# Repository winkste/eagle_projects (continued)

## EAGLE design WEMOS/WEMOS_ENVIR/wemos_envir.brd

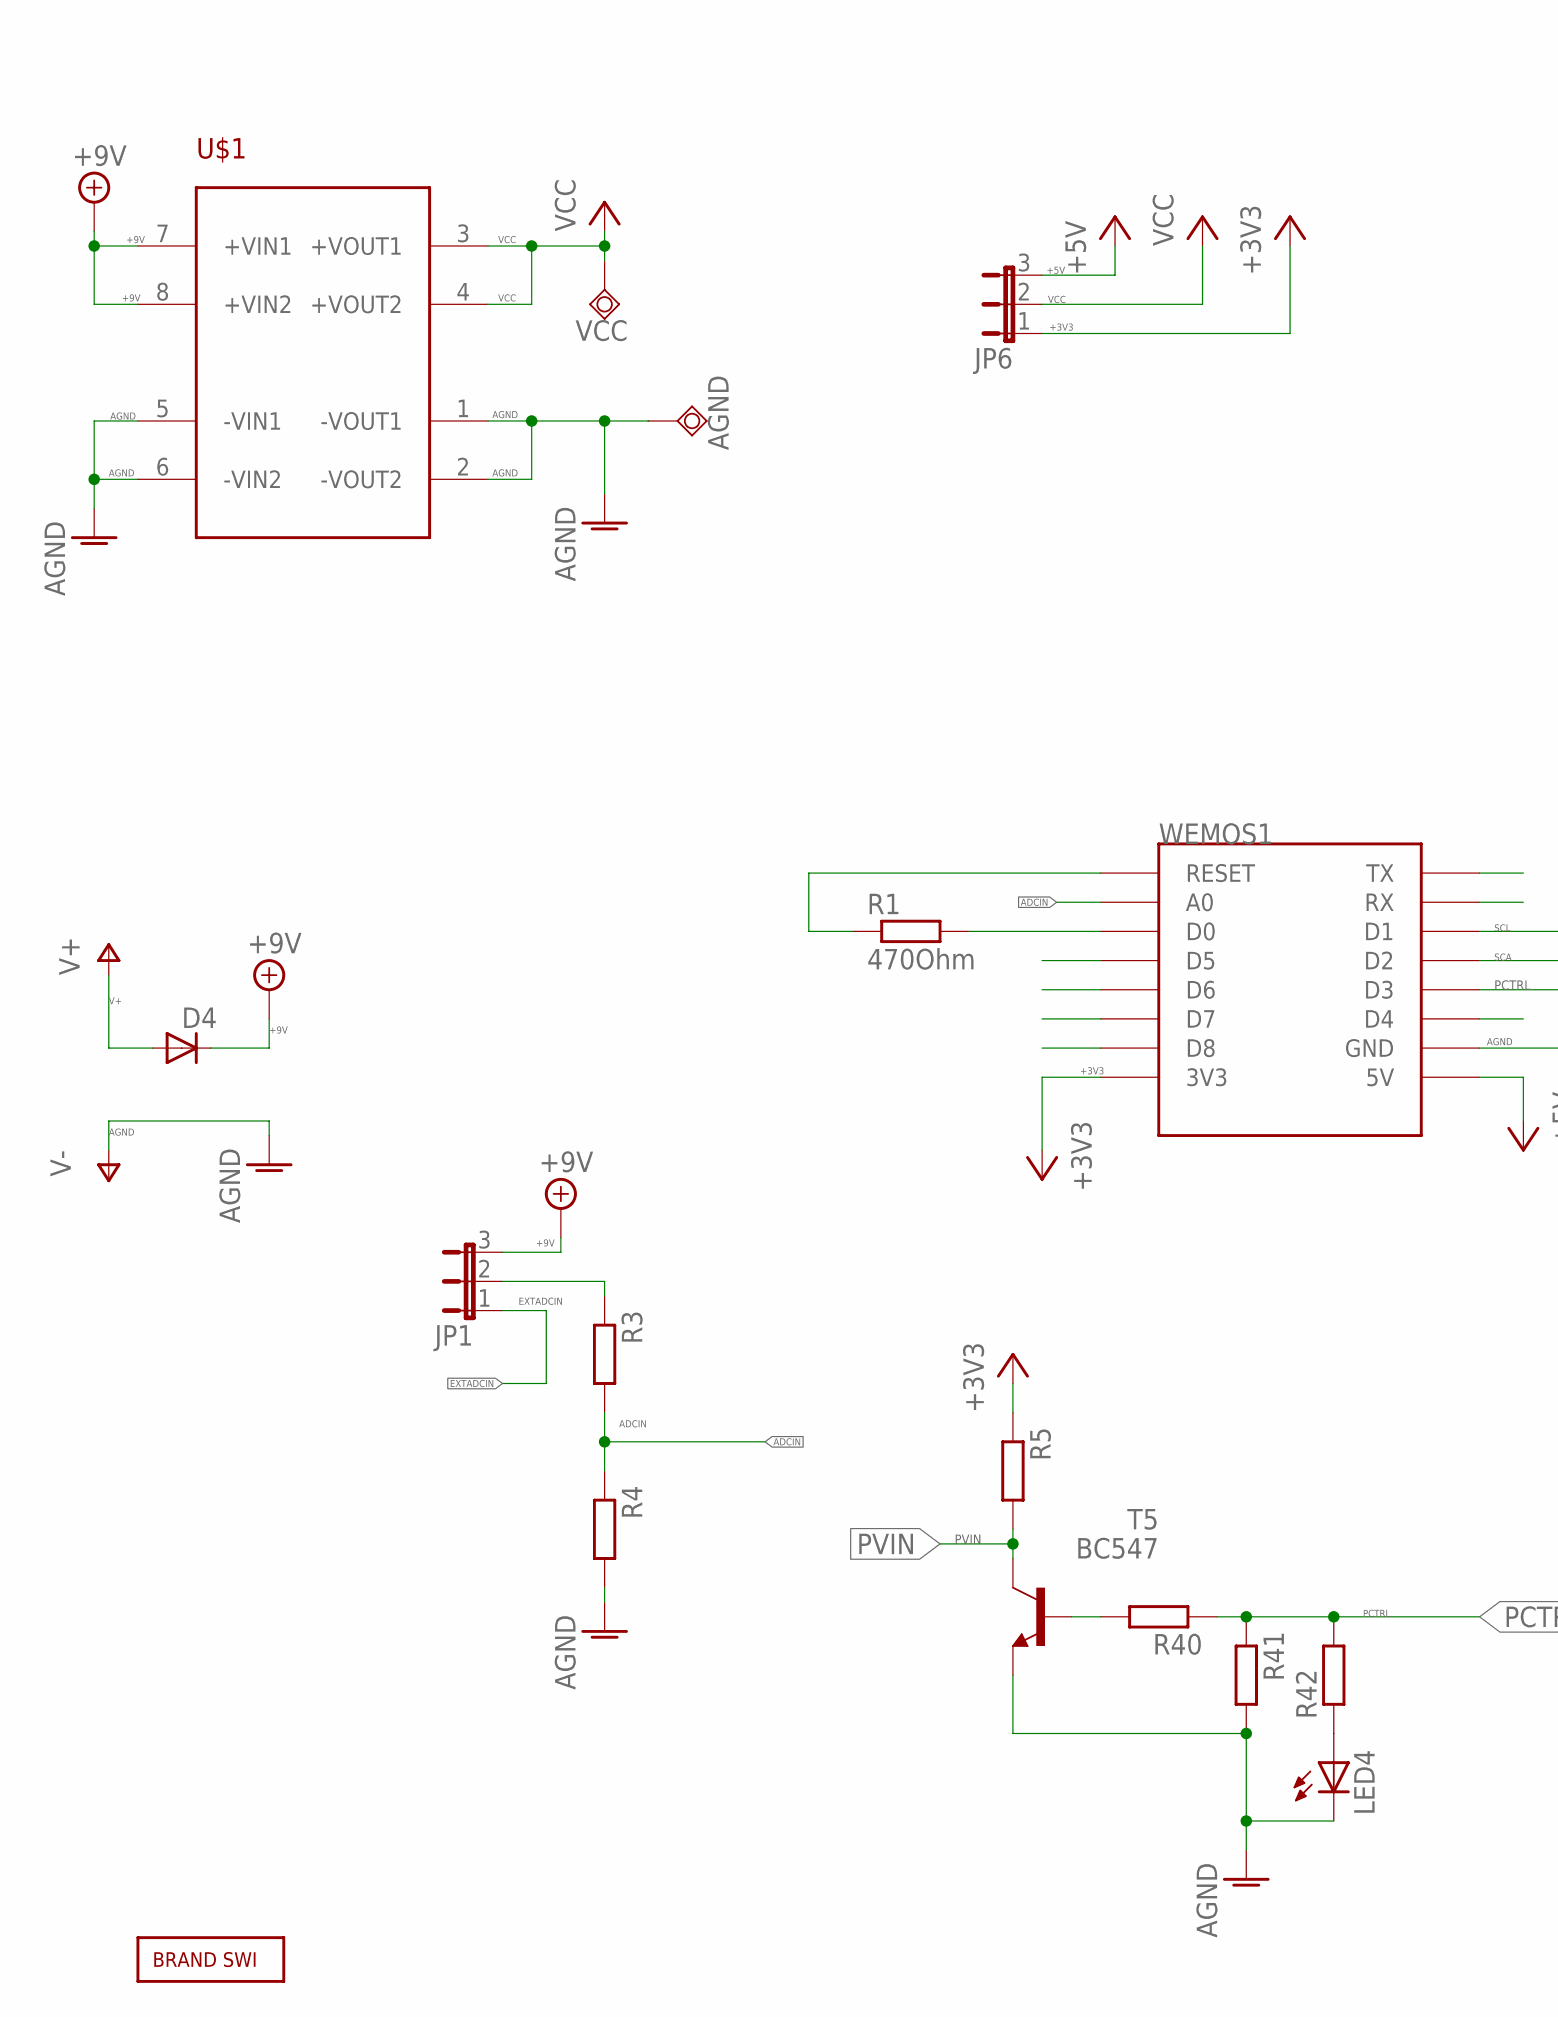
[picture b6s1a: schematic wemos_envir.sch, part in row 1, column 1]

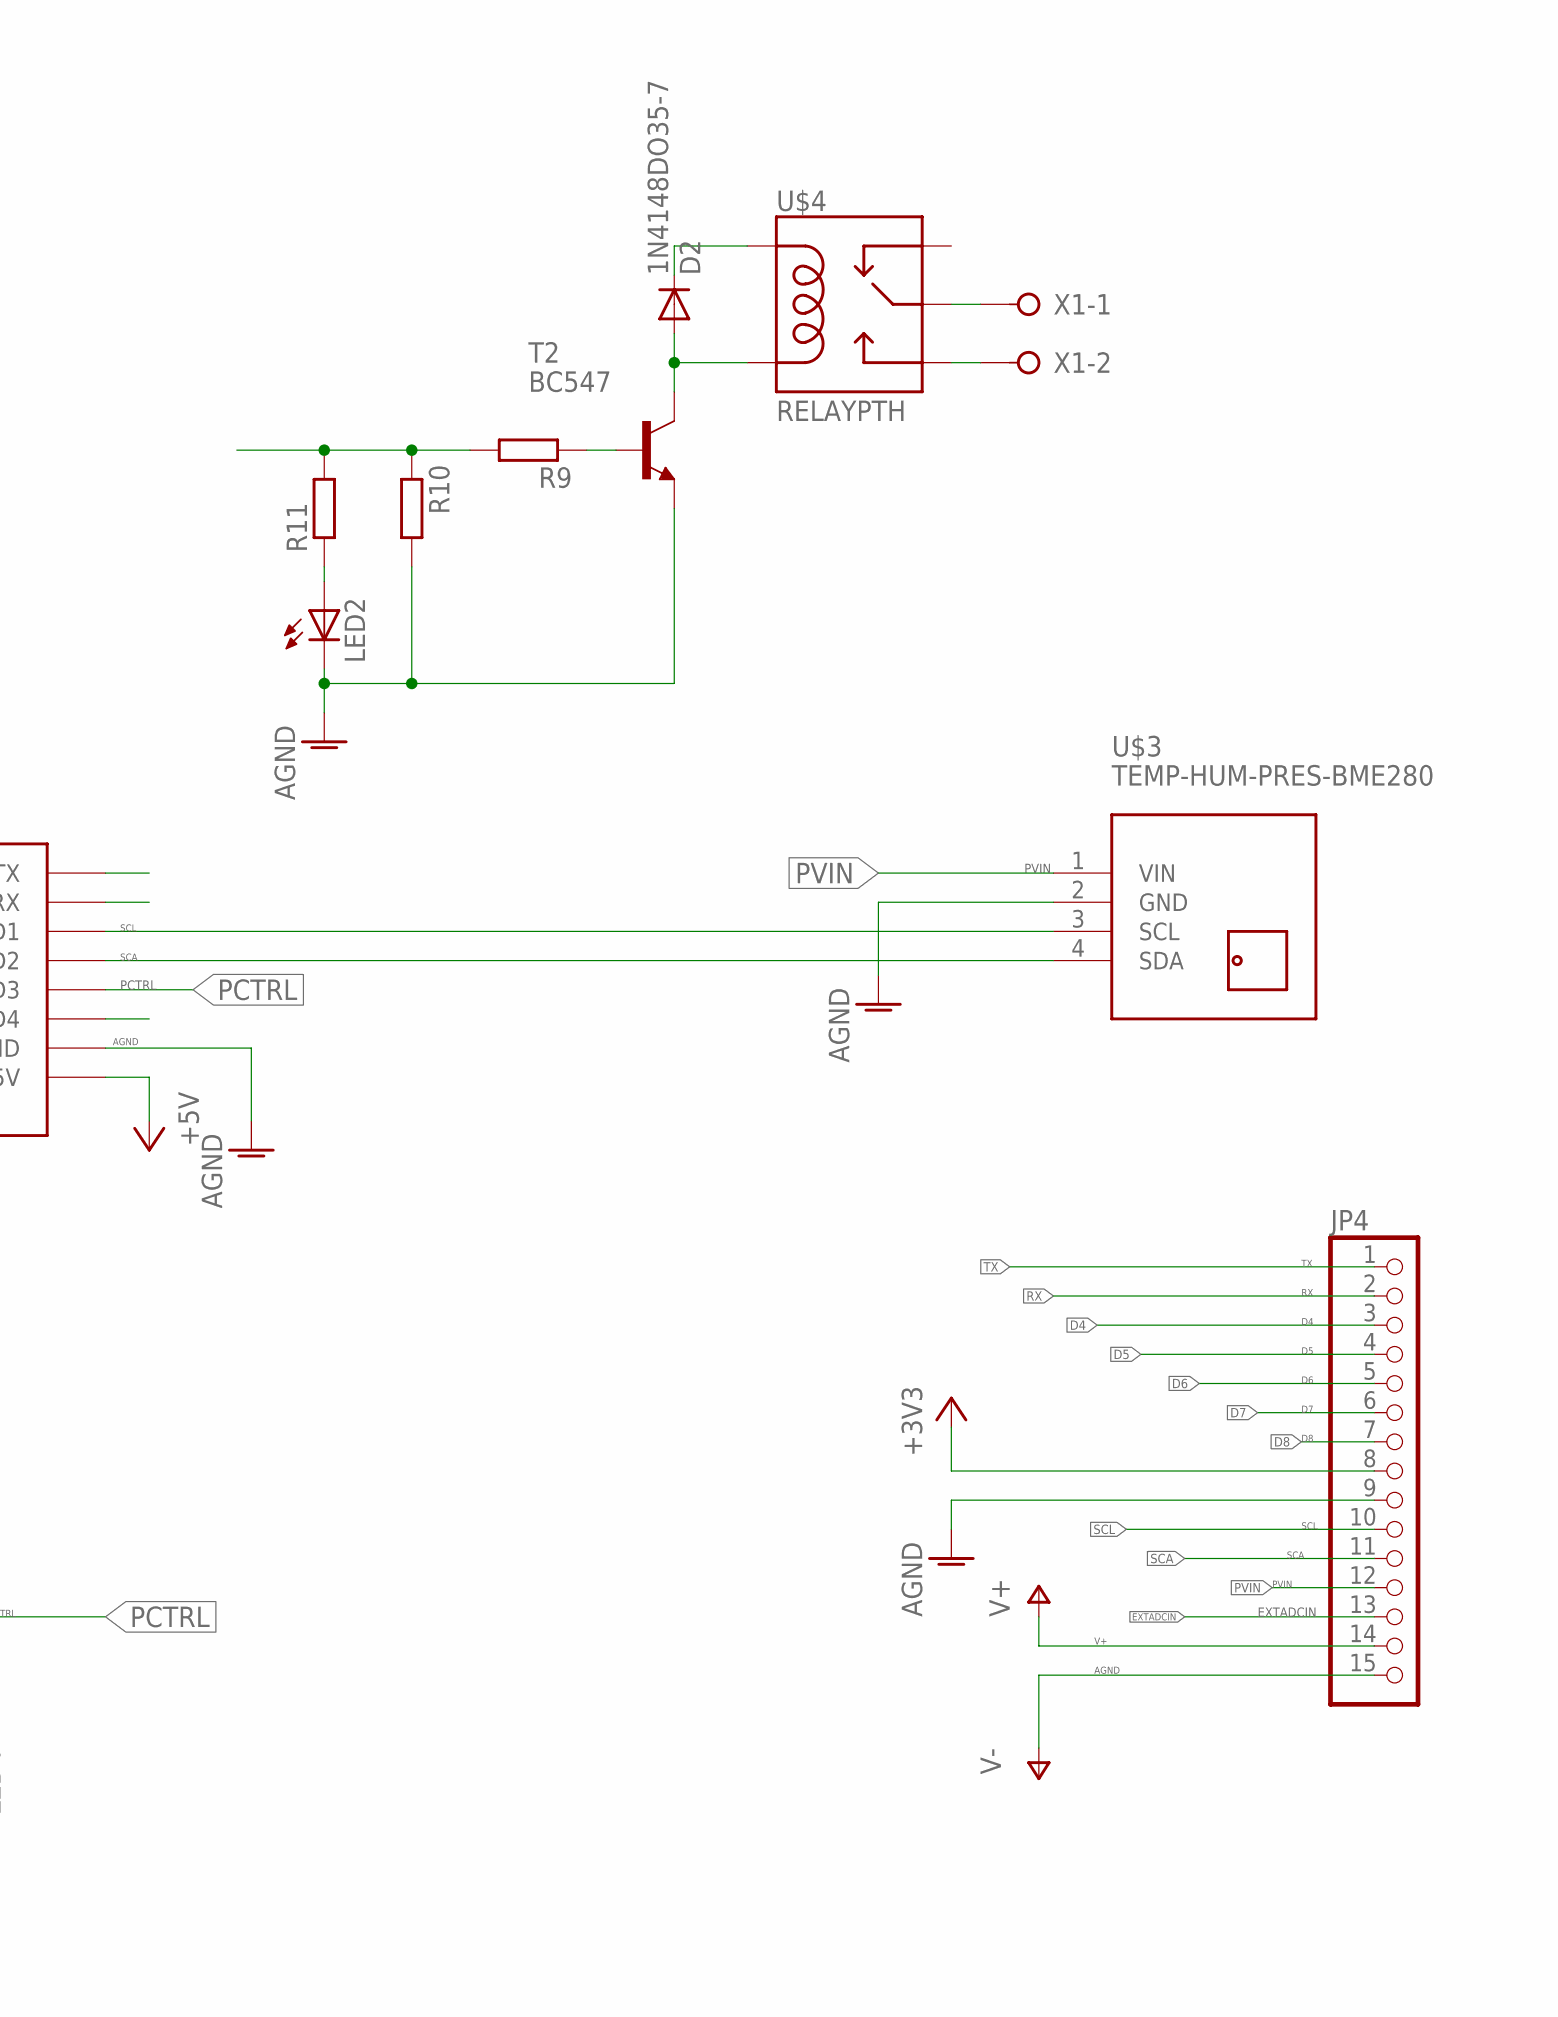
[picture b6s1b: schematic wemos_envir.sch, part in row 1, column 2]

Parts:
AGND: TPSQTP20SQ; TP20SQ
D2, D4: 1N4148DO35-7; DO35-7
JP1, JP6: JP2E; JP2
JP4: PINHD-1X15; 1X15
LED2, LED4: LEDCHIP-LED0805; CHIP-LED0805
R1: 470Ohm; R0805
R3, R4, R5, R9, R10, R11, R40, R41, R42: R-EU_R0805; R0805
T2, T5: BC547; TO92
U$1: LVPS
U$2: BRAND_SWI5X7; BRAND_SWI_5X7
U$3: TEMP-HUM-PRES-BME280
U$4: RELAYPTH; SRD-05VDC-SL-C
VCC: TPSQTP20SQ; TP20SQ
WEMOS1: WEMOS-D1-MINI
X1: W237-02P; W237-132

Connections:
+3V3: JP4.8, JP6.1, R5.1
+5V: JP6.3
+9V: D4.C, JP1.3, U$1.7 (+VIN1), U$1.8 (+VIN2)
ADCIN: R3.2, R4.1, WEMOS1.A0
AGND: AGND.TP, JP4.9, JP4.15, LED2.C, LED4.C, R4.2, R10.2, R41.2, T2.1 (E), T5.1 (E), U$1.2 (-VOUT2), U$1.5 (-VIN1), U$1.6 (-VIN2), U$3.2 (GND)
D4: JP4.3, WEMOS1.D4
D5: JP4.4, WEMOS1.D5
D6: JP4.5, WEMOS1.D6
D7: JP4.6, WEMOS1.D7
D8: JP4.7, WEMOS1.D8
EXTADCIN: JP1.1, JP4.13
unnamed: JP1.2, R3.1
unnamed: R1.2, WEMOS1.D0
unnamed: D2.C, U$4.COIL1
unnamed: D2.A, T2.3 (C), U$4.COIL0
unnamed: R9.1, T2.2 (B)
unnamed: R9.2, R10.1, R11.2
unnamed: LED2.A, R11.1
unnamed: U$4.SWOPEN, X1.2
unnamed: U$4.SWCOMMON, X1.1
unnamed: R1.1, WEMOS1.RESET
unnamed: R40.2, T5.2 (B)
unnamed: LED4.A, R42.1
PCTRL: R40.1, R41.1, R42.2, WEMOS1.D3
PVIN: JP4.12, R5.2, T5.3 (C), U$3.1 (VIN)
RX: JP4.2, WEMOS1.RX
SCA: JP4.11, U$3.4 (SDA), WEMOS1.D2
SCL: JP4.10, U$3.3 (SCL), WEMOS1.D1
TX: JP4.1, WEMOS1.TX
V+: D4.A, JP4.14
VCC: JP6.2, U$1.3 (+VOUT1), U$1.4 (+VOUT2), VCC.TP

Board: 2 copper layers, 27 parts (13 on the bottom side), 30 nets, no tracks yet.

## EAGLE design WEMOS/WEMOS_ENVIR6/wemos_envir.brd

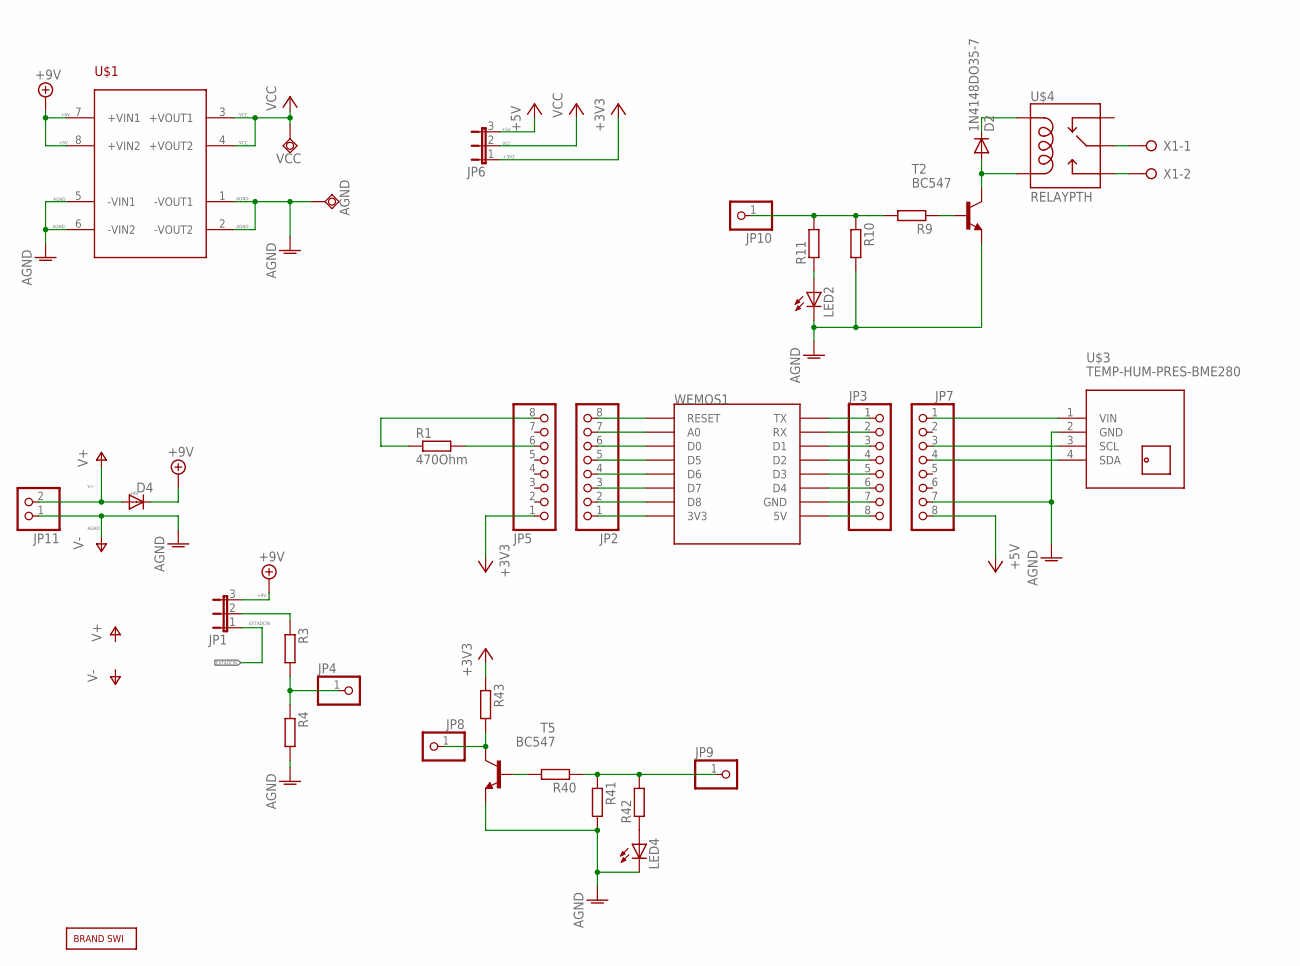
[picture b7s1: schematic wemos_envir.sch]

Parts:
AGND: TPSQTP20SQ; TP20SQ
D2, D4: 1N4148DO35-7; DO35-7
JP1, JP6: JP2E; JP2
JP2, JP3, JP5, JP7: PINHD-1X8; 1X08
JP4, JP8, JP9, JP10: PINHD-1X1; 1X01
JP11: PINHD-1X2; 1X02
LED2, LED4: LEDCHIP-LED0805; CHIP-LED0805
R1: 470Ohm; R0805
R3, R4, R9, R10, R11, R40, R41, R42, R43: R-EU_R0805; R0805
T2, T5: BC547; TO92
U$1: LVPS
U$2: BRAND_SWI5X7; BRAND_SWI_5X7
U$3: TEMP-HUM-PRES-BME280
U$4: RELAYPTH; SRD-05VDC-SL-C
VCC: TPSQTP20SQ; TP20SQ
WEMOS1: WEMOS-D1-MINI
X1: W237-02P; W237-132

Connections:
+3V3: JP5.1, JP6.1, R43.1
+5V: JP6.3, JP7.8
+9V: D4.C, JP1.3, U$1.7 (+VIN1), U$1.8 (+VIN2)
ADCIN: JP4.1, R3.2, R4.1
AGND: AGND.TP, JP7.7, JP11.1, LED2.C, LED4.C, R4.2, R10.2, R41.2, T2.1 (E), T5.1 (E), U$1.2 (-VOUT2), U$1.5 (-VIN1), U$1.6 (-VIN2), U$3.2 (GND)
EXTADCIN: JP1.1
unnamed: JP1.2, R3.1
unnamed: JP5.6, R1.2
unnamed: D2.C, U$4.COIL1
unnamed: D2.A, T2.3 (C), U$4.COIL0
unnamed: R9.1, T2.2 (B)
unnamed: JP10.1, R9.2, R10.1, R11.2
unnamed: LED2.A, R11.1
unnamed: U$4.SWOPEN, X1.2
unnamed: U$4.SWCOMMON, X1.1
unnamed: JP5.8, R1.1
unnamed: JP2.7, WEMOS1.A0
unnamed: JP2.8, WEMOS1.RESET
unnamed: JP2.6, WEMOS1.D0
unnamed: JP2.5, WEMOS1.D5
unnamed: JP2.4, WEMOS1.D6
unnamed: JP2.3, WEMOS1.D7
unnamed: JP2.2, WEMOS1.D8
unnamed: JP2.1, WEMOS1.3V3
unnamed: JP3.3, WEMOS1.D1
unnamed: JP3.4, WEMOS1.D2
unnamed: JP3.1, WEMOS1.TX
unnamed: JP3.2, WEMOS1.RX
unnamed: JP3.6, WEMOS1.D4
unnamed: JP3.7, WEMOS1.GND
unnamed: JP3.8, WEMOS1.5V
unnamed: JP3.5, WEMOS1.D3
unnamed: R40.2, T5.2 (B)
unnamed: JP7.1, U$3.1 (VIN)
unnamed: LED4.A, R42.1
PCTRL: JP9.1, R40.1, R41.1, R42.2
PVIN: JP8.1, R43.2, T5.3 (C)
SCA: JP7.4, U$3.4 (SDA)
SCL: JP7.3, U$3.3 (SCL)
V+: D4.A, JP11.2
VCC: JP6.2, U$1.3 (+VOUT1), U$1.4 (+VOUT2), VCC.TP

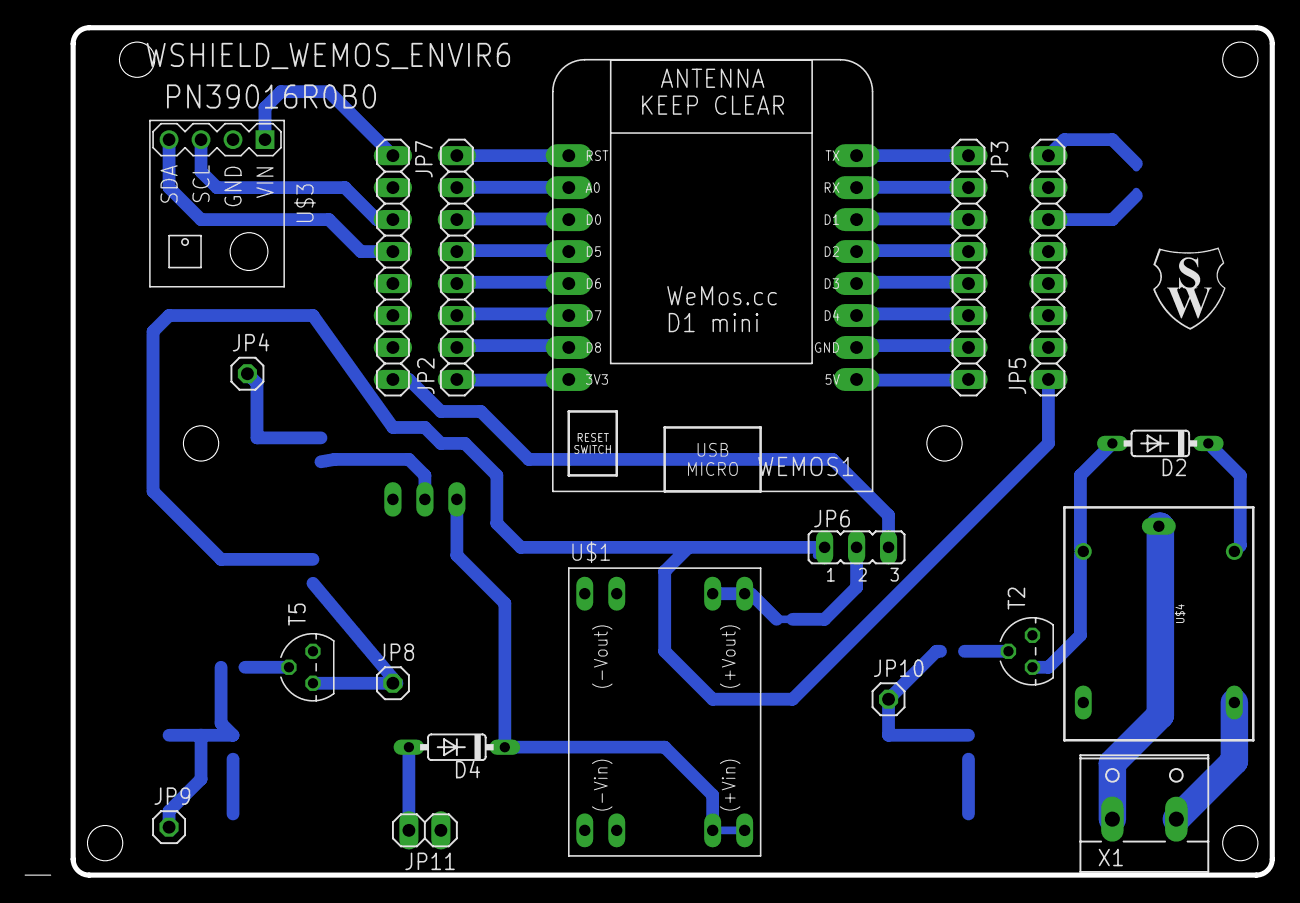
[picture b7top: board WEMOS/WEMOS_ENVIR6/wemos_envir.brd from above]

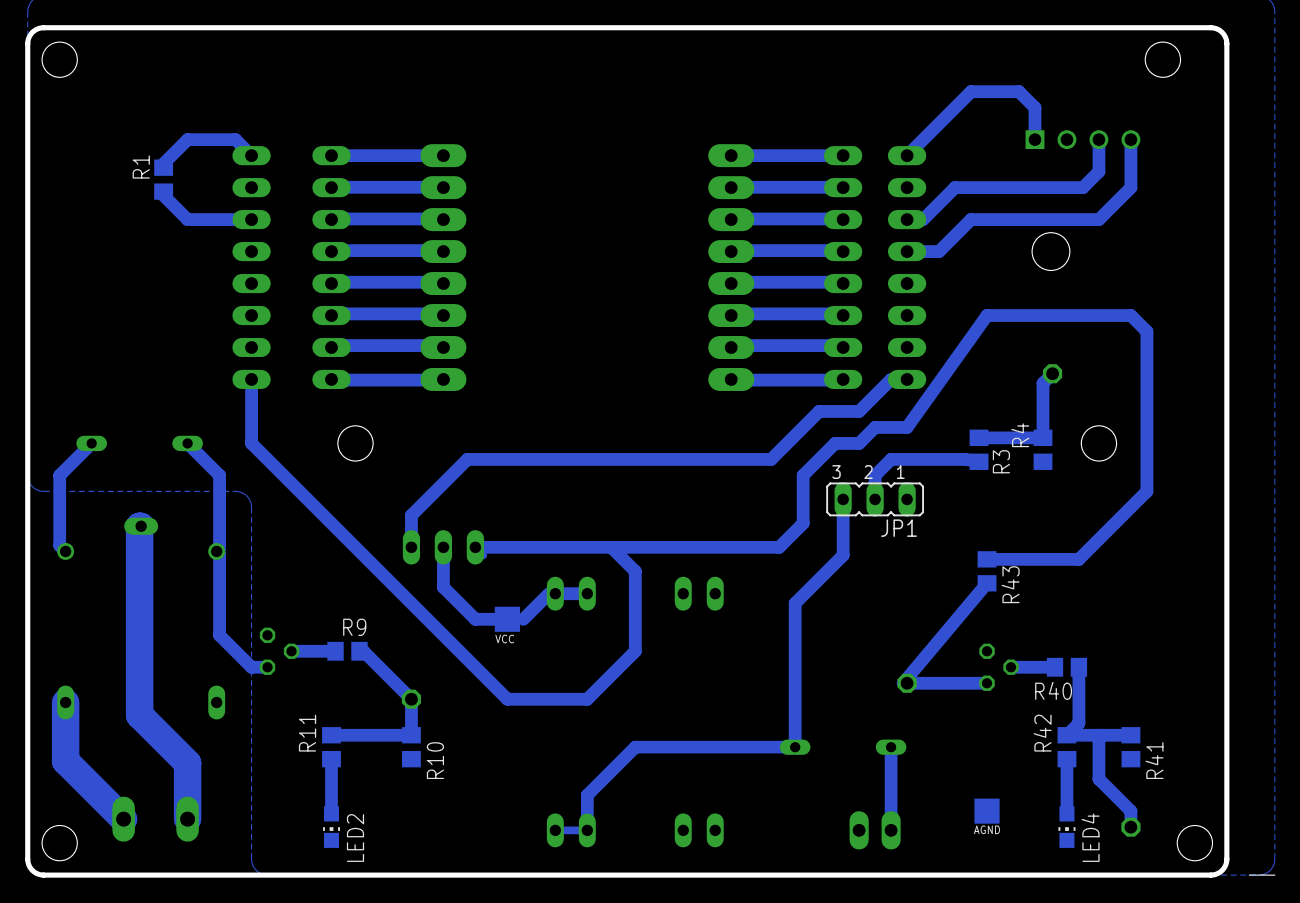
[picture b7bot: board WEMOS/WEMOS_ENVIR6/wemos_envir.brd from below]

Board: 2 copper layers, 99.1 x 67.3 mm, 35 parts (15 on the bottom side), 40 nets.

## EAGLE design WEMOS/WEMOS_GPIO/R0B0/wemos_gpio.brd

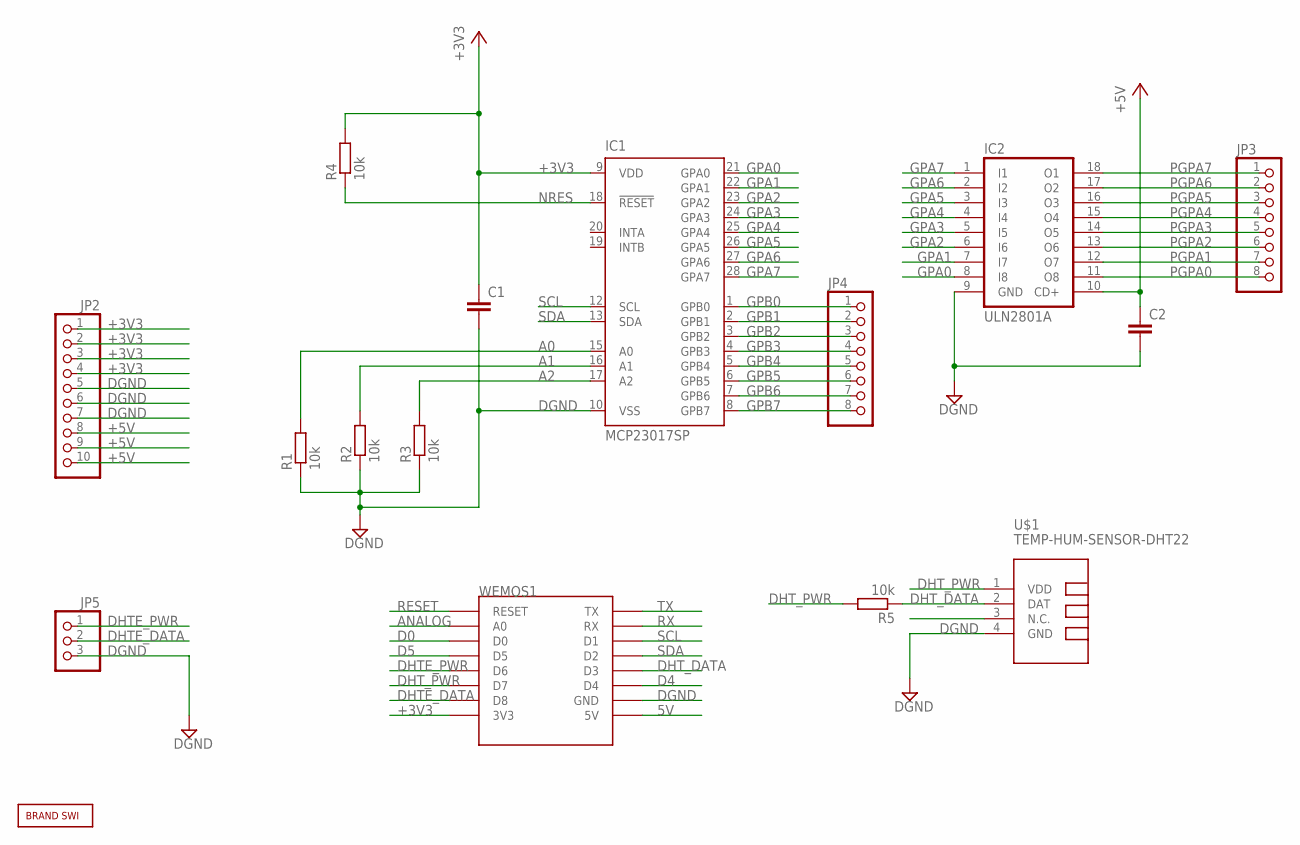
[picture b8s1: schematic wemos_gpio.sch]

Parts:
C1, C2: C-EUC1210; C1210
IC1: MCP23017SP; DIL28-3
IC2: ULN2801A; DIL18
JP2: PINHD-1X10; 1X10
JP3, JP4: PINHD-1X8; 1X08
JP5: PINHD-1X3; 1X03
R1, R2, R3, R4, R5: 10k; M1206
U$1: TEMP-HUM-SENSOR-DHT22
U$2: BRAND_SWI5X7; BRAND_SWI_5X7
WEMOS1: WEMOS-D1-MINI

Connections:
5V: WEMOS1.5V
+3V3: C1.1, IC1.9 (VDD), JP2.1, JP2.2, JP2.3, JP2.4, R4.2, WEMOS1.3V3
+5V: C2.1, IC2.10 (CD+), JP2.8, JP2.9, JP2.10
A0: IC1.15 (A0), R1.2
A1: IC1.16 (A1), R2.2
A2: IC1.17 (A2), R3.2
ANALOG: WEMOS1.A0
D0: WEMOS1.D0
D4: WEMOS1.D4
D5: WEMOS1.D5
DGND: C1.2, C2.2, IC1.10 (VSS), IC2.9 (GND), JP2.5, JP2.6, JP2.7, JP5.3, R1.1, R2.1, R3.1, U$1.4 (GND), WEMOS1.GND
DHTE_DATA: JP5.2, WEMOS1.D8
DHTE_PWR: JP5.1, WEMOS1.D6
DHT_DATA: R5.1, U$1.2 (DAT), WEMOS1.D3
DHT_PWR: R5.2, U$1.1 (VDD), WEMOS1.D7
GPA0: IC1.21 (GPA0), IC2.8 (I8)
GPA1: IC1.22 (GPA1), IC2.7 (I7)
GPA2: IC1.23 (GPA2), IC2.6 (I6)
GPA3: IC1.24 (GPA3), IC2.5 (I5)
GPA4: IC1.25 (GPA4), IC2.4 (I4)
GPA5: IC1.26 (GPA5), IC2.3 (I3)
GPA6: IC1.27 (GPA6), IC2.2 (I2)
GPA7: IC1.28 (GPA7), IC2.1 (I1)
GPB0: IC1.1 (GPB0), JP4.1
GPB1: IC1.2 (GPB1), JP4.2
GPB2: IC1.3 (GPB2), JP4.3
GPB3: IC1.4 (GPB3), JP4.4
GPB4: IC1.5 (GPB4), JP4.5
GPB5: IC1.6 (GPB5), JP4.6
GPB6: IC1.7 (GPB6), JP4.7
GPB7: IC1.8 (GPB7), JP4.8
NRES: IC1.18 (!RESET), R4.1
PGPA0: IC2.11 (O8), JP3.8
PGPA1: IC2.12 (O7), JP3.7
PGPA2: IC2.13 (O6), JP3.6
PGPA3: IC2.14 (O5), JP3.5
PGPA4: IC2.15 (O4), JP3.4
PGPA5: IC2.16 (O3), JP3.3
PGPA6: IC2.17 (O2), JP3.2
PGPA7: IC2.18 (O1), JP3.1
RESET: WEMOS1.RESET
RX: WEMOS1.RX
SCL: IC1.12 (SCL), WEMOS1.D1
SDA: IC1.13 (SDA), WEMOS1.D2

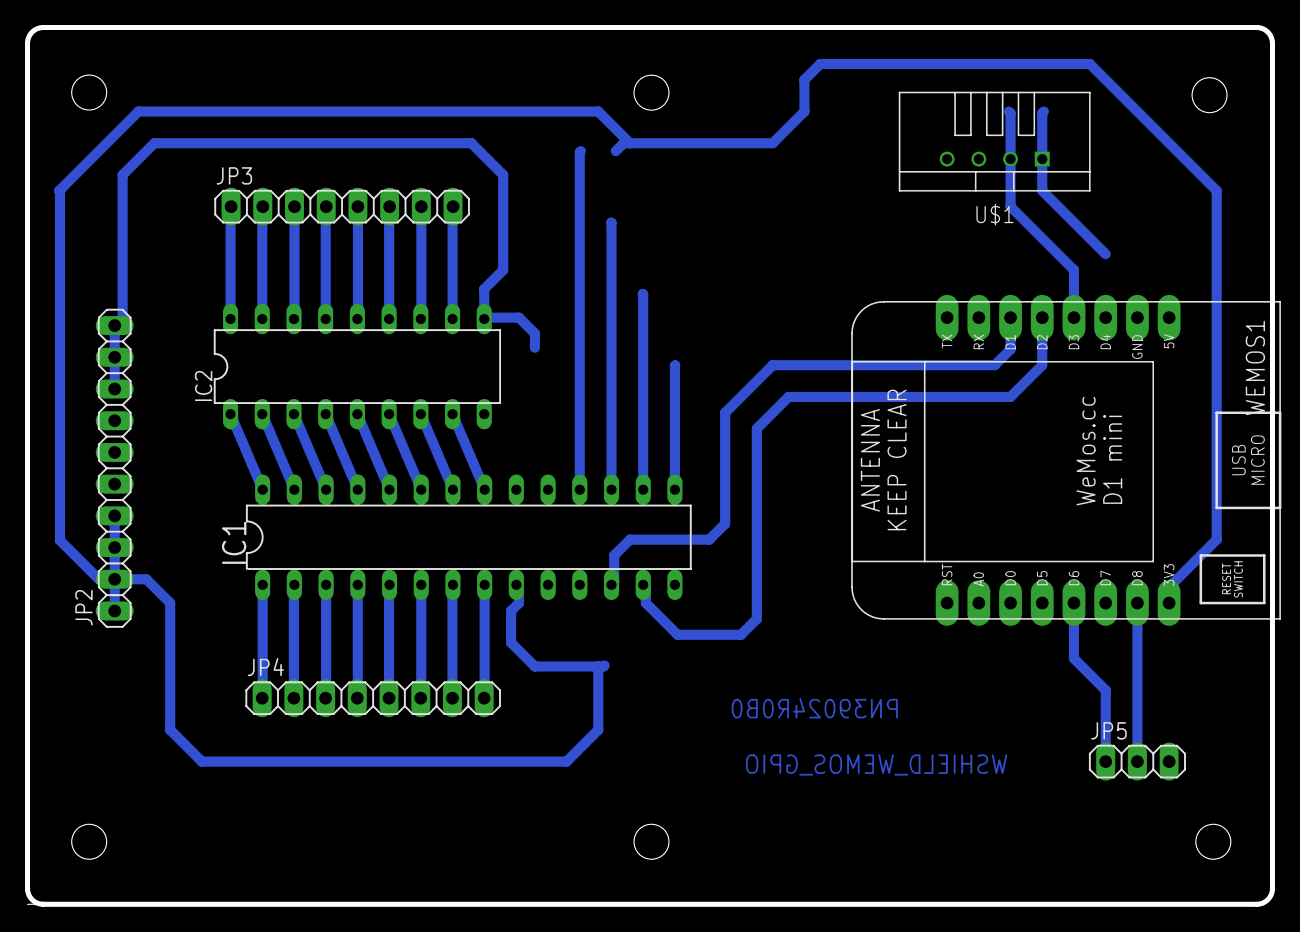
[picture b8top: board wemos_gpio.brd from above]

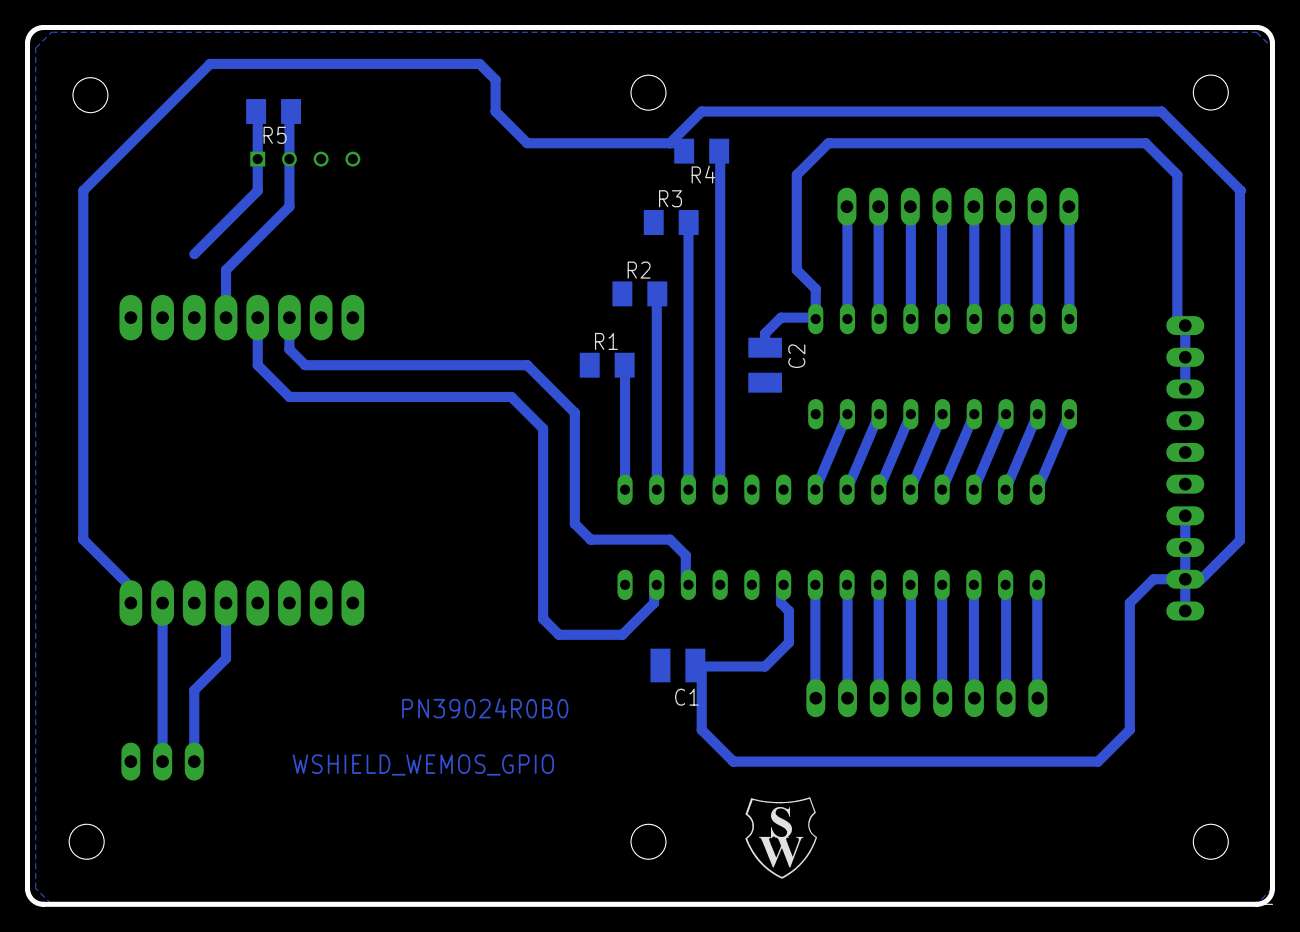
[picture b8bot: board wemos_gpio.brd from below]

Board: 2 copper layers, 99.7 x 70.2 mm, 16 parts (8 on the bottom side), 37 nets.
